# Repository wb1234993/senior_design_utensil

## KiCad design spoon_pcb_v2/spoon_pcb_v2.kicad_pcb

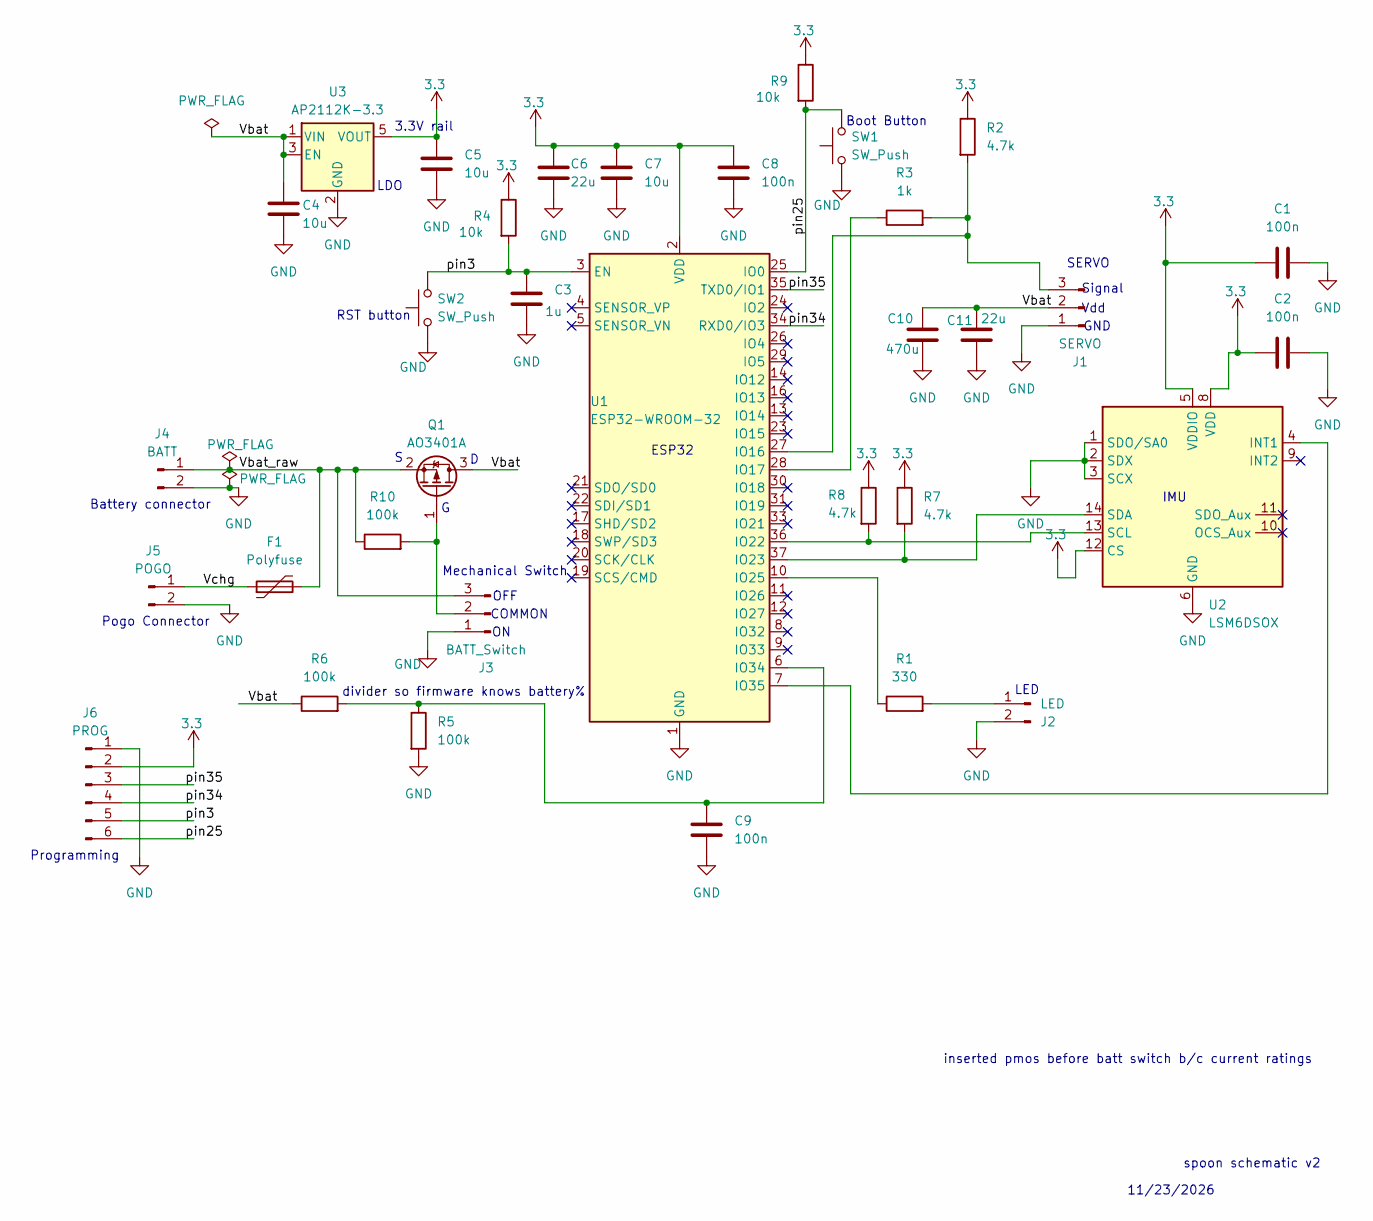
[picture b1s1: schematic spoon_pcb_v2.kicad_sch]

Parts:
C1, C2, C8, C9: 100n; C_0603_1608Metric
C3: 1u; C_0603_1608Metric
C4, C5, C7: 10u; C_0805_2012Metric
C6, C11: 22u; C_1206_3216Metric
C10: 470u; CP_Elec_6.3x7.7
F1: Polyfuse; Fuse_1206_3216Metric
J1: SERVO; JST_EH_S3B-EH_1x03_P2.50mm_Horizontal
J2: LED; JST_PH_S2B-PH-K_1x02_P2.00mm_Horizontal
J3: BATT_Switch; JST_EH_S3B-EH_1x03_P2.50mm_Horizontal
J4: BATT; JST_PH_S2B-PH-K_1x02_P2.00mm_Horizontal
J5: POGO; JST_PH_S2B-PH-K_1x02_P2.00mm_Horizontal
J6: PROG; PinHeader_1x06_P2.54mm_Horizontal
Q1: AO3401A; SOT-23
R1: 330; R_0603_1608Metric
R2, R7, R8: 4.7k; R_0603_1608Metric
R3: 1k; R_0603_1608Metric
R4, R9: 10k; R_0603_1608Metric
R5, R6, R10: 100k; R_0603_1608Metric
SW1, SW2: SW_Push; SW_SPST_PTS810
U1: ESP32-WROOM-32
U2: LSM6DSOX; LGA-14_3x2.5mm_P0.5mm_LayoutBorder3x4y
U3: AP2112K-3.3; SOT-23-5

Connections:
3.3: C1.2, C2.1, C5.1, C6.1, C7.1, C8.1, J6.2, R2.1, R4.1, R7.1, R8.1, R9.1, U1.2 (VDD), U2.5 (VDDIO), U2.8 (VDD), U2.12 (CS), U3.5 (VOUT)
/Vbat: C4.1, C10.1, C11.1, J1.2, Q1.3 (D), R6.1, U3.1 (VIN), U3.3 (EN)
/Vbat_raw: F1.2, J3.3, J4.1, Q1.2 (S), R10.1
/Vchg: F1.1, J5.1
/pin3: C3.1, J6.5, R4.2, SW2.2, U1.3 (EN)
/pin25: J6.6, R9.2, SW1.2, U1.25 (IO0)
/pin34: J6.4, U1.34 (RXD0/IO3)
/pin35: J6.3, U1.35 (TXD0/IO1)
GND: C1.1, C2.2, C3.2, C4.2, C5.2, C6.2, C7.2, C8.2, C9.2, C10.2, C11.2, J1.1, J2.2, J3.1, J4.2, J5.2, J6.1, R5.2, SW1.1, SW2.1, U1.1 (GND), U1.15 (GND), U1.38 (GND), U1.39 (GND), U2.1 (SDO/SA0), U2.2 (SDX), U2.3 (SCX), U2.6 (GND), U2.7 (GND), U3.2 (GND)
unnamed: J1.3, R2.2, R3.2, U1.27 (IO16)
unnamed: J2.1, R1.2
unnamed: J3.2, Q1.1 (G), R10.2
unnamed: R3.1, U1.28 (IO17)
unnamed: R8.2, U1.36 (IO22), U2.13 (SCL)
unnamed: R7.2, U1.37 (IO23), U2.14 (SDA)
unnamed: R1.1, U1.10 (IO25)
unnamed: C9.1, R5.1, R6.2, U1.6 (IO34)
unnamed: U1.7 (IO35), U2.4 (INT1)

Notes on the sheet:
Mechanical Switch
Boot Button
3.3V rail
OFF
Pogo Connector
Signal
Battery connector
RST button
GND
divider so firmware knows battery%
SERVO
IMU
Vdd
ESP32
Programming
spoon schematic v2
inserted pmos before batt switch b/c current ratings
LDO
COMMON
LED
11/23/2026

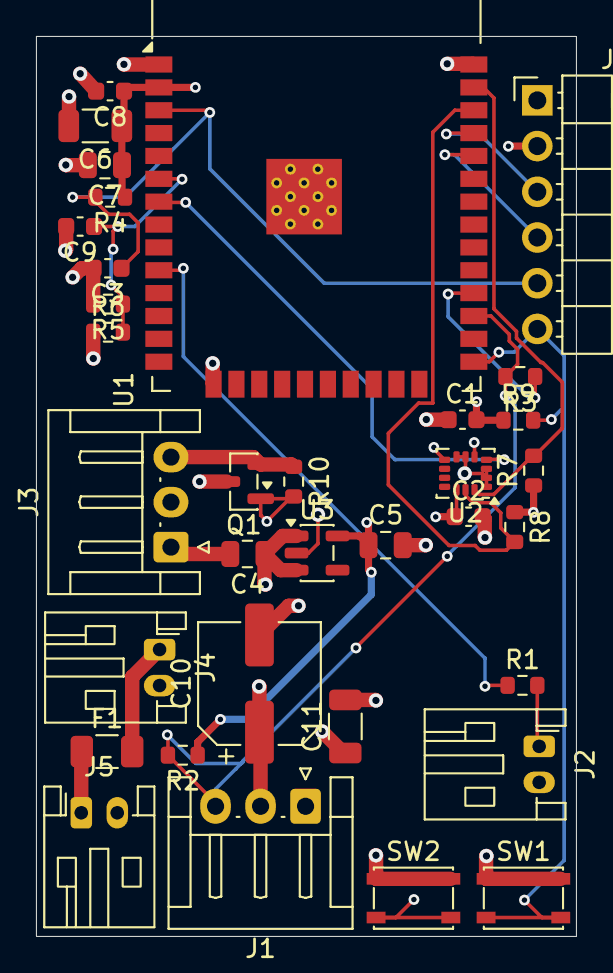
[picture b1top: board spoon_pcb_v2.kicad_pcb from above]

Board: 4 copper layers, 30.0 x 50.0 mm, 34 parts (0 on the bottom side), 18 nets.
